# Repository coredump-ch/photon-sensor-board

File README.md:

# Photon Sensor Board

A board to easily connect a Particle Photon with a DS18B20 temparature sensor.

The ``particle-boards`` library can be found here:
https://github.com/coredump-ch/kicad-particle

**Order here:**

- [DirtyPCBs](http://dirtypcbs.com/view.php?share=14221&accesskey=f6b3ffa6a66b2c59bf8eb13904b6e816)

## Screenshot

## PCB

DirtyPCB production:

Poorly self etched PCB:

## Assembly

- Solder 2x12 pin headers to the photon pins.
- Solder the resistor onto the board.
- Solder a DS18B20 sensor to the board using a cable / wire. Make sure it's long
  enough (<30cm) to prevent self-heating of the sensor.
  On the screenshot of the PCB above, the bottom pin is GND (blue), the middle
  one is Data (yellow) and the top pin is VDD (red). You can find the pin
  numbering of the sensor [here](http://mikroshop.ch/?gruppe=6&artikel=30).

## License

MIT

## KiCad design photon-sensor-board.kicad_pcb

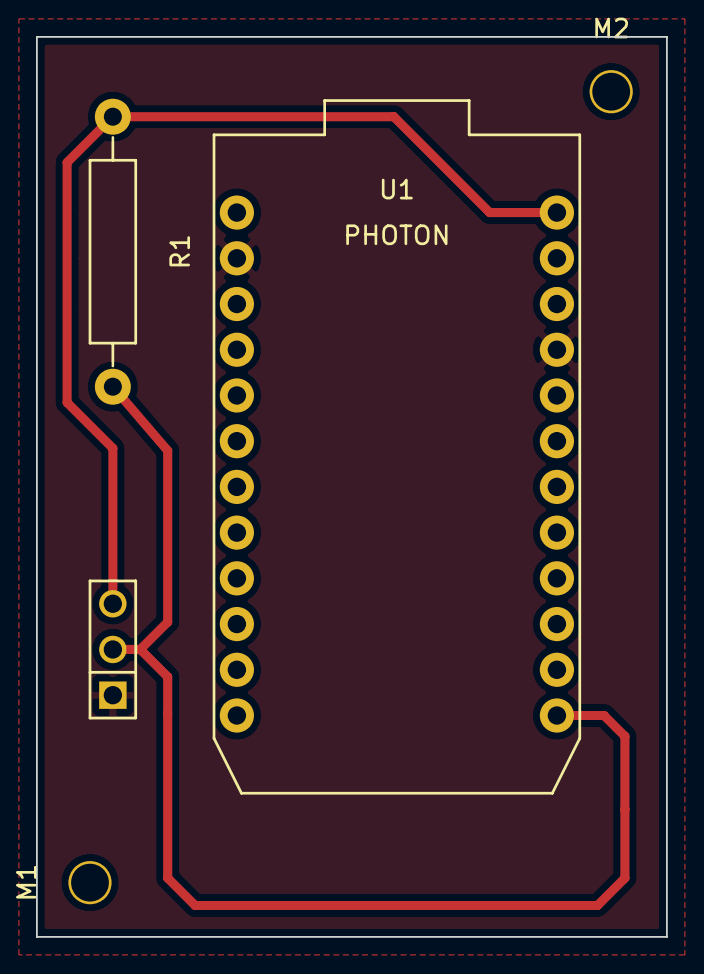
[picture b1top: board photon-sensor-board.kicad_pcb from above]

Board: 2 copper layers, 35.0 x 50.0 mm, 5 parts (0 on the bottom side), 3 nets.

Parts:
M1, M2: MountingHole_2-5mm
R1: 4.7kΩ; Resistor_Horizontal_RM15mm
U1: PHOTON; photon
U2: DS18B20; PIN_ARRAY_3X1

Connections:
GND: U1.2, U1.21, U2.1
unnamed: R1.1, U1.24, U2.3
unnamed: R1.2, U1.13, U2.2

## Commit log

2015-10-02 Fixes
2015-10-02 Added mounting holes
2015-10-03 Upgraded project for KiCad 2015-10-02 BZR 6241
2015-10-03 Updated netlist
2015-10-03 Removed border around mounting holes
2015-10-03 Adjusted OSHW text
2015-10-04 Updated some footprints with new libraries
2015-10-04 Some adjustments
2015-10-04 Added selfetch version
2015-10-15 Added PCB pic
2015-12-01 Exported v1.2
2015-12-01 Update screenshot
2016-01-11 Added DirtyPCB photo and assembly instructions
2016-07-19 Update README.md
    Sensor should *not* be soldered directly onto the board.
2016-08-09 Add firmware link to README
